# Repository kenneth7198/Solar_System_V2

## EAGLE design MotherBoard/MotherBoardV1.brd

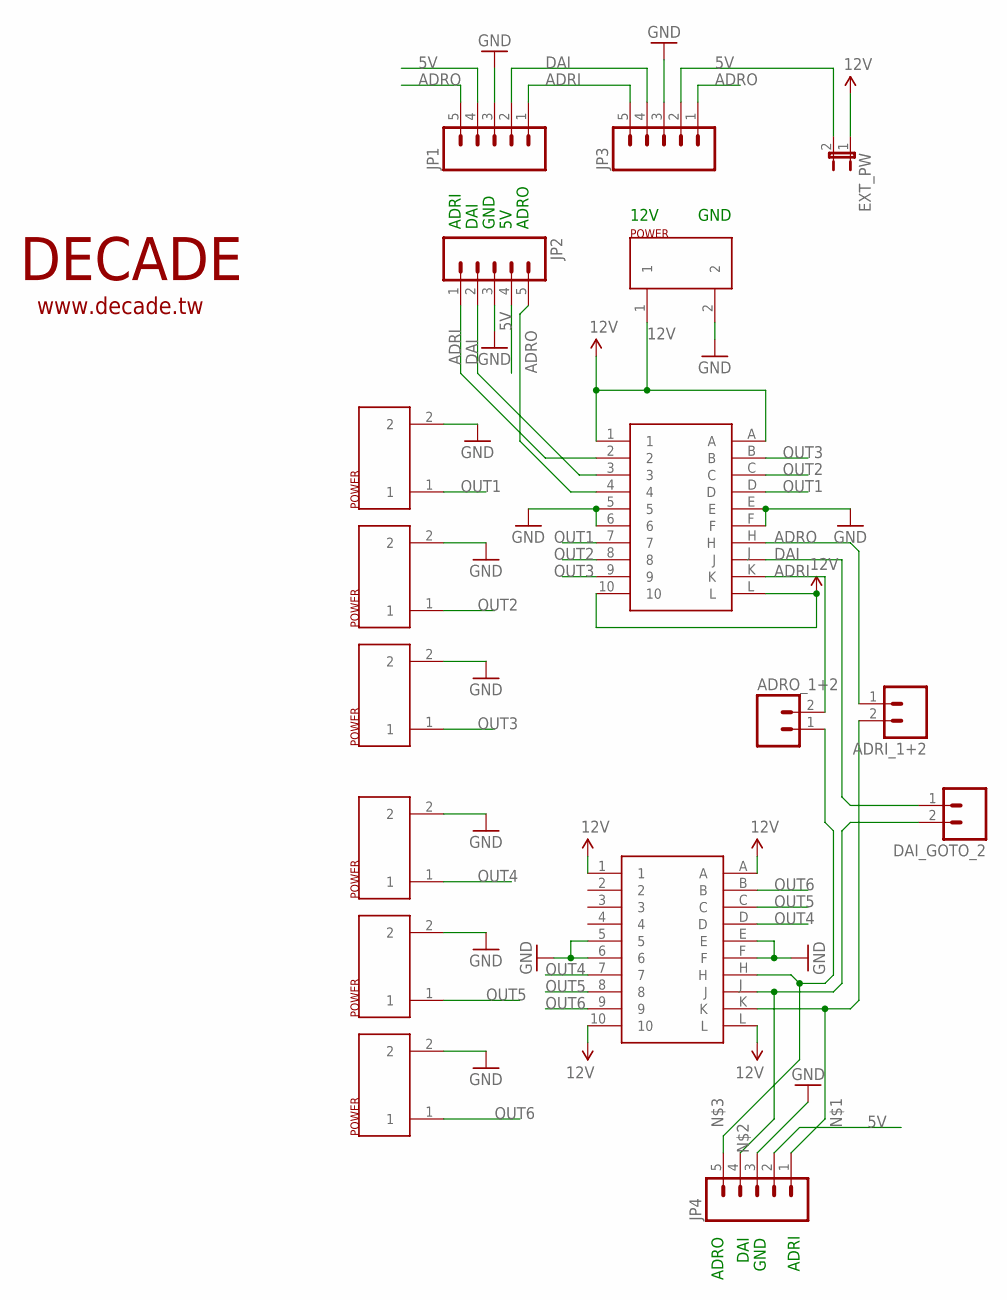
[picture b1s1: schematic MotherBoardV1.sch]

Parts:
ADRI_1+2: M02LOCK; 1X02_LOCK
ADRO_1+2: M02LOCK; 1X02_LOCK
DAI_GOTO_2: M02LOCK; 1X02_LOCK
EXT_PW: JUMPER-2SMD-NO; SJ_2S-NO
JP1, JP2, JP3, JP4: M05SCREW; SCREWTERMINAL-3.5MM-5
U$1, U$2, U$3, U$5, U$6, U$7, U$8: 1X02_POWER_9MM; 1X02_9MM_POWER
U$4, U$9: LW-N10A2G
U$11: DECADE-LOGO-SMALL

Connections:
5V: EXT_PW.2, JP1.4, JP2.4, JP3.2, JP4.2
12V: EXT_PW.1, U$4.1, U$4.10, U$4.A, U$4.L, U$5.1, U$9.1, U$9.10, U$9.A, U$9.L
ADRI: ADRO_1+2.2, JP1.1, JP2.1, JP3.5, U$4.2, U$4.K
ADRO: ADRI_1+2.1, JP1.5, JP2.5, JP3.1, U$4.4, U$4.H
DAI: DAI_GOTO_2.1, JP1.2, JP2.2, JP3.4, U$4.3, U$4.J
GND: JP1.3, JP2.3, JP3.3, JP4.3, U$1.2, U$2.2, U$3.2, U$4.5, U$4.6, U$4.E, U$4.F, U$5.2, U$6.2, U$7.2, U$8.2, U$9.5, U$9.6, U$9.E, U$9.F
unnamed: ADRI_1+2.2, JP4.1, U$9.K
unnamed: DAI_GOTO_2.2, JP4.4, U$9.J
unnamed: ADRO_1+2.1, JP4.5, U$9.H
OUT1: U$1.1, U$4.7, U$4.D
OUT2: U$2.1, U$4.8, U$4.C
OUT3: U$3.1, U$4.9, U$4.B
OUT4: U$6.1, U$9.7, U$9.D
OUT5: U$7.1, U$9.8, U$9.C
OUT6: U$8.1, U$9.9, U$9.B

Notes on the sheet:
12V
GND
ADRI
DAI
ADRO

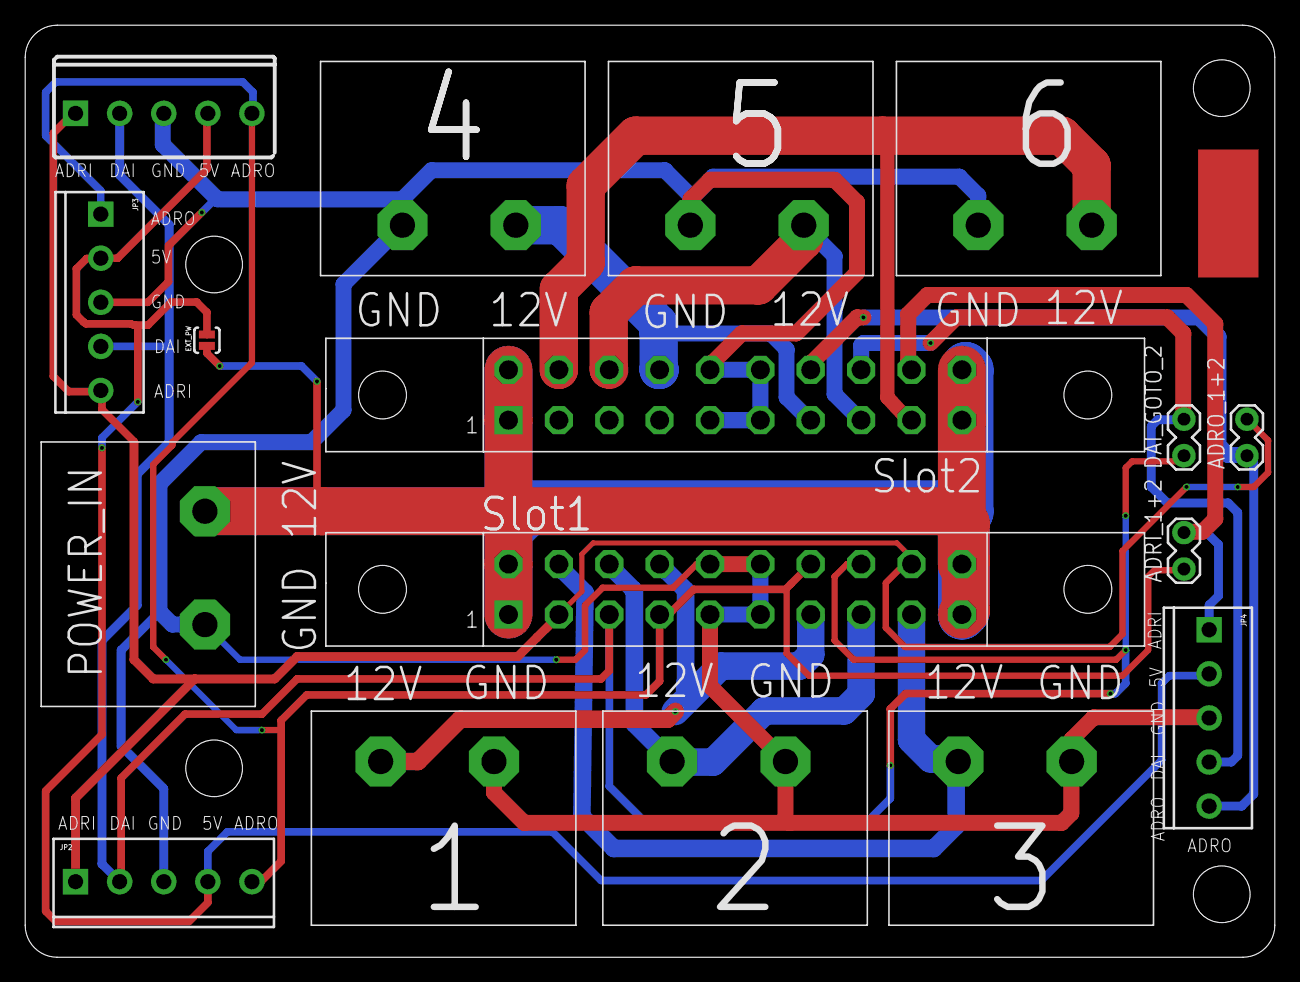
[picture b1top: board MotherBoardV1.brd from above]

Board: 2 copper layers, 99.2 x 74.0 mm, 18 parts (1 on the bottom side), 15 nets.

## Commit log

2015-12-02 motherBoard

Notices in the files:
parts and their libraries:
DECADE-libraries20151104: Licensing: Creative Commons ShareAlike 4.0 International - https://creativecommons.org/licenses/by-sa/4.0
